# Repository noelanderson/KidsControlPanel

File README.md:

# KidsControlPanel
Octonaut's inspired vehicle control panel with flight yoke and standard instruments

Javascript application runs instrument cluster on Raspberry Pi displaying on a (800x400) lcd panel

Custom RP2040 based hardware runs the remaining panel functions

RP2040 board appears as a HID joystick and uses a VL6180X ranging sensor to measure pitch, and an AS5600 magnetic Rotation Sensor to measure roll.

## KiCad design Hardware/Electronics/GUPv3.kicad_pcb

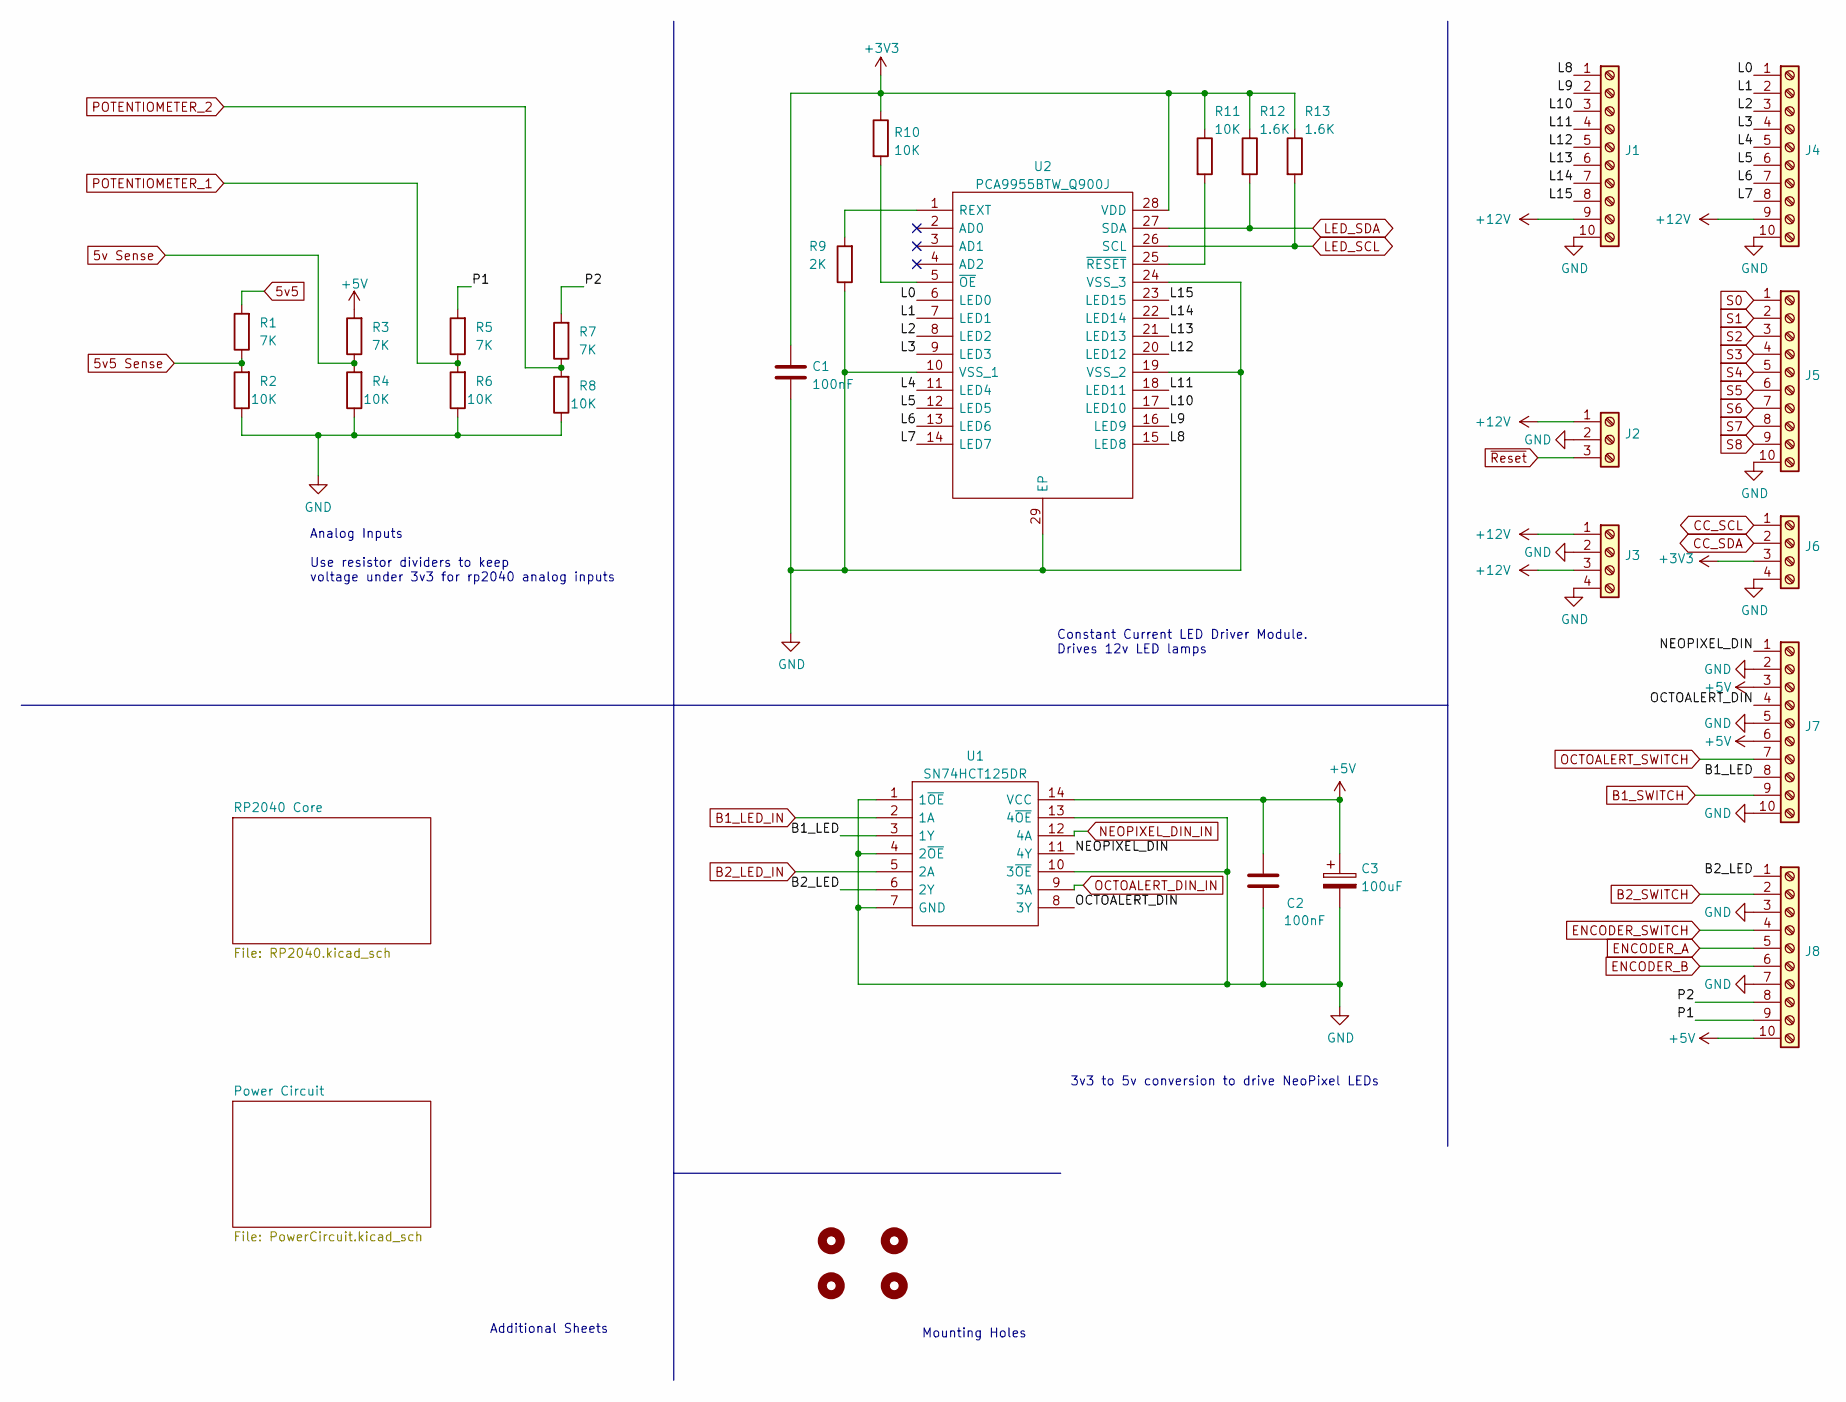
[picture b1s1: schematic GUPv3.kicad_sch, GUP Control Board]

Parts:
C1, C2: 100nF; C_1206_3216Metric_Pad1.33x1.80mm_HandSolder
C3: 100uF; C_1206_3216Metric_Pad1.33x1.80mm_HandSolder
H1, H2, H3, H4: M2.5; MountingHole_2.7mm_M2.5_DIN965_Pad
J1, J4, J5, J7, J8: Screw_Terminal_01x10; CUI_TB002-500-10BE
J2: Screw_Terminal_01x03; CUI_TB002-500-03BE
J3, J6: Screw_Terminal_01x04; CUI_TB002-500-04BE
R1, R3, R5, R7: 7K; R_1206_3216Metric_Pad1.30x1.75mm_HandSolder
R2, R4, R6, R8, R10, R11: 10K; R_1206_3216Metric_Pad1.30x1.75mm_HandSolder
R9: 2K; R_1206_3216Metric_Pad1.30x1.75mm_HandSolder
R12, R13: 1.6K; R_1206_3216Metric_Pad1.30x1.75mm_HandSolder
U1: SN74HCT125DR; SOIC127P600X175-14N; Mouser Part Number 595-SN74HCT125DR
U2: PCA9955BTW_Q900J; SOP65P640X110-29N_thermal_vias; Mouser Part Number 771-PCA9955BTW/Q900J

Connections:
5v5: R1.2; also elsewhere on the board
5v5 Sense: R1.1, R2.2; also elsewhere on the board
5v Sense: R3.1, R4.2; also elsewhere on the board
+3V3: C1.1, J6.3, R10.1, R11.1, R12.1, R13.1, U2.28 (VDD); also elsewhere on the board
+5V: C2.1, C3.1, J7.3, J7.6, J8.10, R3.2, U1.14 (VCC); also elsewhere on the board
+12V: J1.9, J2.1, J3.1, J3.3, J4.9; also elsewhere on the board
/B1_LED: J7.8, U1.3 (1Y)
/B2_LED: J8.1, U1.6 (2Y)
/L0: J4.1, U2.6 (LED0)
/L1: J4.2, U2.7 (LED1)
/L2: J4.3, U2.8 (LED2)
/L3: J4.4, U2.9 (LED3)
/L4: J4.5, U2.11 (LED4)
/L5: J4.6, U2.12 (LED5)
/L6: J4.7, U2.13 (LED6)
/L7: J4.8, U2.14 (LED7)
/L8: J1.1, U2.15 (LED8)
/L9: J1.2, U2.16 (LED9)
/L10: J1.3, U2.17 (LED10)
/L11: J1.4, U2.18 (LED11)
/L12: J1.5, U2.20 (LED12)
/L13: J1.6, U2.21 (LED13)
/L14: J1.7, U2.22 (LED14)
/L15: J1.8, U2.23 (LED15)
/NEOPIXEL_DIN: J7.1, U1.11 (4Y)
/OCTOALERT_DIN: J7.4, U1.8 (3Y)
/P1: J8.9, R5.2
/P2: J8.8, R7.2
B1_LED_IN: U1.2 (1A); also elsewhere on the board
B1_SWITCH: J7.9; also elsewhere on the board
B2_LED_IN: U1.5 (2A); also elsewhere on the board
B2_SWITCH: J8.2; also elsewhere on the board
CC_SCL: J6.1; also elsewhere on the board
CC_SDA: J6.2; also elsewhere on the board
ENCODER_A: J8.5; also elsewhere on the board
ENCODER_B: J8.6; also elsewhere on the board
ENCODER_SWITCH: J8.4; also elsewhere on the board
GND: C1.2, C2.2, C3.2, J1.10, J2.2, J3.2, J3.4, J4.10, J5.10, J6.4, J7.2, J7.5, J7.10, J8.3, J8.7, R2.1, R4.1, R6.1, R8.1, R9.1, U1.1 (1~OE), U1.4 (2~OE), U1.7 (GND), U1.10 (3~OE), U1.13 (4~OE), U2.10 (VSS_1), U2.19 (VSS_2), U2.24 (VSS_3), U2.29 (EP); also elsewhere on the board
LED_SCL: R13.2, U2.26 (SCL); also elsewhere on the board
LED_SDA: R12.2, U2.27 (SDA); also elsewhere on the board
NEOPIXEL_DIN_IN: U1.12 (4A); also elsewhere on the board
unnamed: R9.2, U2.1 (REXT)
unnamed: R10.2, U2.5 (~OE)
unnamed: R11.2, U2.25 (~RESET)
OCTOALERT_DIN_IN: U1.9 (3A); also elsewhere on the board
OCTOALERT_SWITCH: J7.7; also elsewhere on the board
POTENTIOMETER_1: R5.1, R6.2; also elsewhere on the board
POTENTIOMETER_2: R7.1, R8.2; also elsewhere on the board
S0: J5.1; also elsewhere on the board
S1: J5.2; also elsewhere on the board
S2: J5.3; also elsewhere on the board
S3: J5.4; also elsewhere on the board
S4: J5.5; also elsewhere on the board
S5: J5.6; also elsewhere on the board
S6: J5.7; also elsewhere on the board
S7: J5.8; also elsewhere on the board
S8: J5.9; also elsewhere on the board
~Reset: J2.3; also elsewhere on the board

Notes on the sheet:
3v3 to 5v conversion to drive NeoPixel LEDs
Analog Inputs Use resistor dividers to keep voltage under 3v3 for rp2040 analog inputs
Constant Current LED Driver Module. Drives 12v LED lamps
Additional Sheets
Mounting Holes

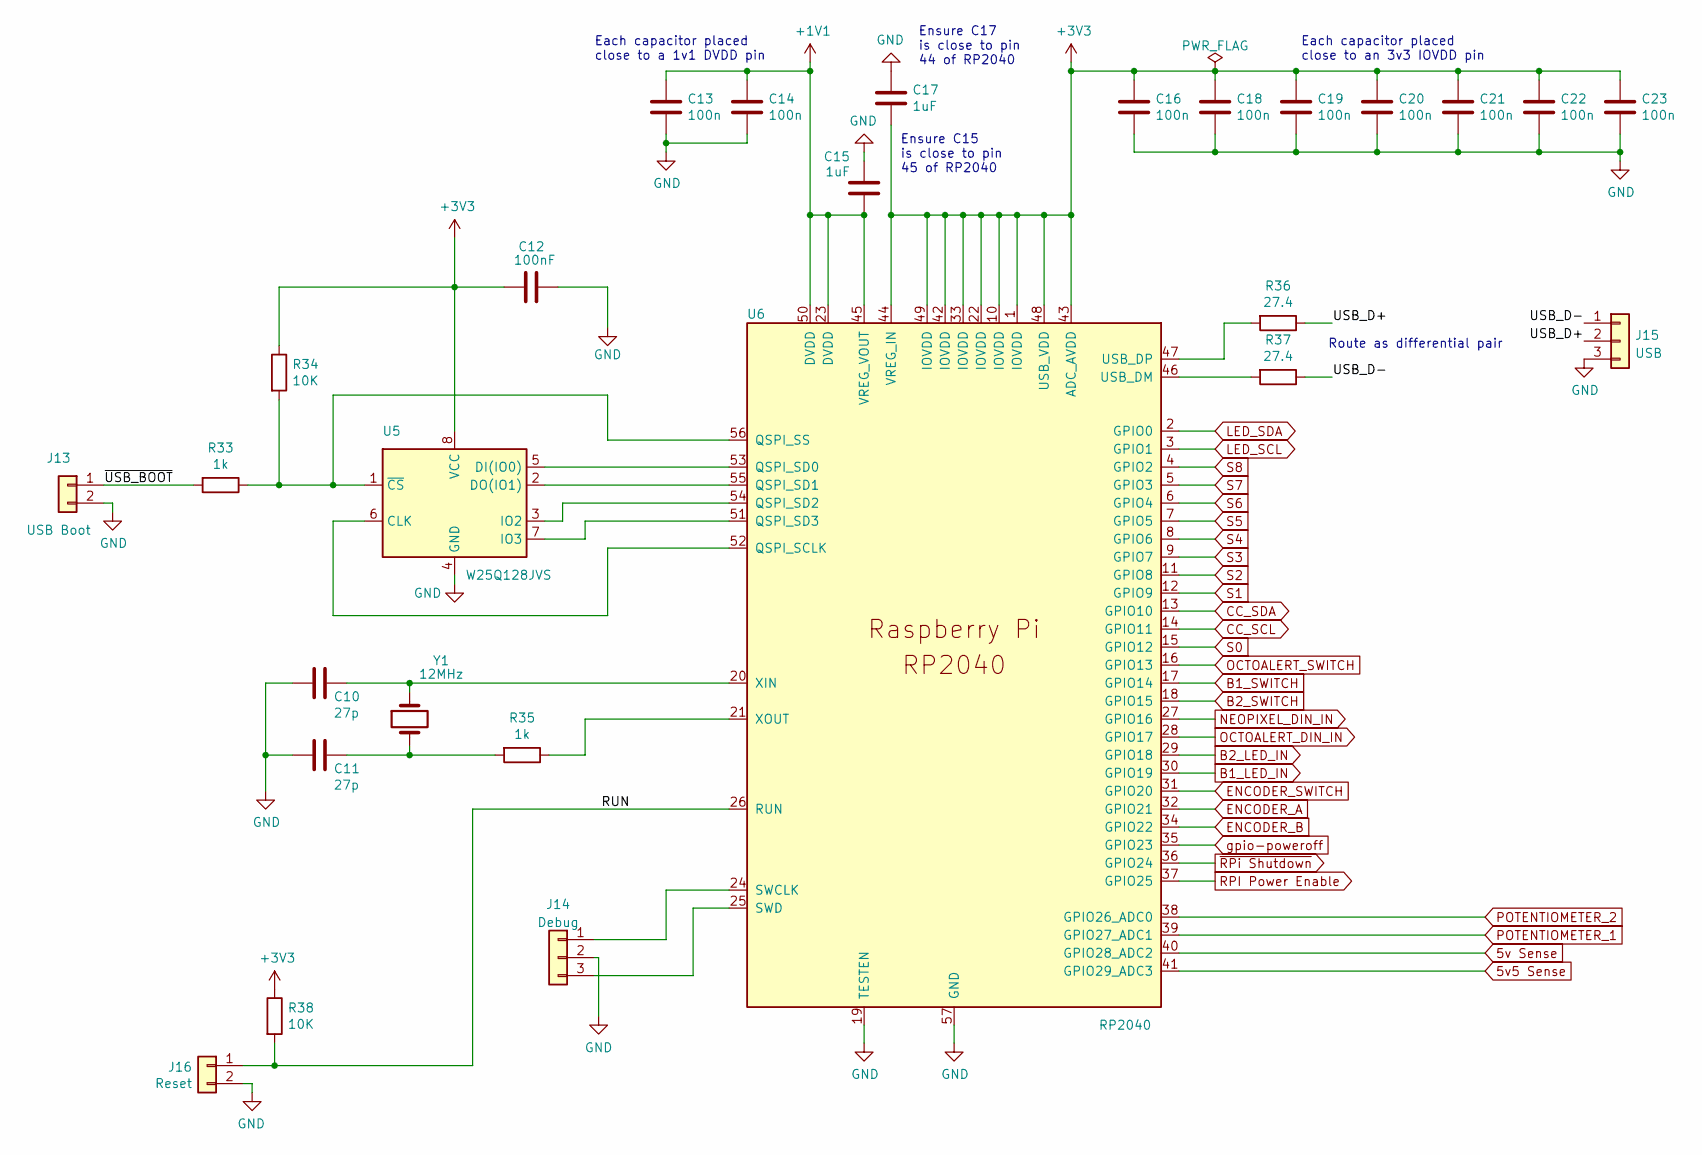
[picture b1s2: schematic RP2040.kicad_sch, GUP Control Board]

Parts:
C10, C11: 27p; C_1206_3216Metric_Pad1.33x1.80mm_HandSolder
C12: 100nF; C_1206_3216Metric_Pad1.33x1.80mm_HandSolder
C13, C14, C16, C18, C19, C20, C21, C22, C23: 100n; C_0603_1608Metric_Pad1.08x0.95mm_HandSolder
C15, C17: 1uF; C_0603_1608Metric_Pad1.08x0.95mm_HandSolder
J13: USB Boot; PinHeader_1x02_P2.54mm_Vertical
J14: Debug; PinHeader_1x03_P2.54mm_Vertical
J15: USB; PinHeader_1x03_P2.54mm_Vertical
J16: Reset; PinHeader_1x02_P2.54mm_Vertical
R33: 1k; R_1206_3216Metric_Pad1.30x1.75mm_HandSolder
R34: 10K; R_1206_3216Metric_Pad1.30x1.75mm_HandSolder
R35: 1k; R_0603_1608Metric_Pad0.98x0.95mm_HandSolder
R36, R37: 27.4; R_0603_1608Metric_Pad0.98x0.95mm_HandSolder
R38: 10K; R_0603_1608Metric_Pad0.98x0.95mm_HandSolder
U5: W25Q128JVS; SOIC127P790X216-8N
U6: RP2040; RP2040-QFN-56
Y1: 12MHz; ABLS7M216000MHZD2YT; Digi-Key_PN 535-13415-1-ND

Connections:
5v5 Sense: U6.41 (GPIO29_ADC3); also elsewhere on the board
5v Sense: U6.40 (GPIO28_ADC2); also elsewhere on the board
+1V1: C13.1, C14.1, C15.1, U6.23 (DVDD), U6.45 (VREG_VOUT), U6.50 (DVDD)
+3V3: C12.2, C16.1, C17.2, C18.1, C19.1, C20.1, C21.1, C22.1, C23.1, R34.1, R38.1, U5.8 (VCC), U6.1 (IOVDD), U6.10 (IOVDD), U6.22 (IOVDD), U6.33 (IOVDD), U6.42 (IOVDD), U6.43 (ADC_AVDD), U6.44 (VREG_IN), U6.48 (USB_VDD), U6.49 (IOVDD); also elsewhere on the board
/RP2040 Core/RUN: J16.1, R38.2, U6.26 (RUN)
/RP2040 Core/USB_D+: J15.2, R36.1
/RP2040 Core/USB_D-: J15.1, R37.1
/RP2040 Core/~USB_BOOT: J13.1, R33.2
B1_LED_IN: U6.30 (GPIO19); also elsewhere on the board
B1_SWITCH: U6.17 (GPIO14); also elsewhere on the board
B2_LED_IN: U6.29 (GPIO18); also elsewhere on the board
B2_SWITCH: U6.18 (GPIO15); also elsewhere on the board
CC_SCL: U6.14 (GPIO11); also elsewhere on the board
CC_SDA: U6.13 (GPIO10); also elsewhere on the board
ENCODER_A: U6.32 (GPIO21); also elsewhere on the board
ENCODER_B: U6.34 (GPIO22); also elsewhere on the board
ENCODER_SWITCH: U6.31 (GPIO20); also elsewhere on the board
GND: C10.2, C11.2, C12.1, C13.2, C14.2, C15.2, C16.2, C17.1, C18.2, C19.2, C20.2, C21.2, C22.2, C23.2, J13.2, J14.2, J15.3, J16.2, U5.4 (GND), U6.19 (TESTEN), U6.57 (GND); also elsewhere on the board
LED_SCL: U6.3 (GPIO1); also elsewhere on the board
LED_SDA: U6.2 (GPIO0); also elsewhere on the board
NEOPIXEL_DIN_IN: U6.27 (GPIO16); also elsewhere on the board
unnamed: C10.1, U6.20 (XIN), Y1.1
unnamed: C11.1, R35.2, Y1.2
unnamed: J14.1, U6.24 (SWCLK)
unnamed: J14.3, U6.25 (SWD)
unnamed: R33.1, R34.2, U5.1 (~CS), U6.56 (QSPI_SS)
unnamed: R35.1, U6.21 (XOUT)
unnamed: R36.2, U6.47 (USB_DP)
unnamed: R37.2, U6.46 (USB_DM)
unnamed: U5.2 (DO(IO1)), U6.55 (QSPI_SD1)
unnamed: U5.3 (IO2), U6.54 (QSPI_SD2)
unnamed: U5.5 (DI(IO0)), U6.53 (QSPI_SD0)
unnamed: U5.6 (CLK), U6.52 (QSPI_SCLK)
unnamed: U5.7 (IO3), U6.51 (QSPI_SD3)
OCTOALERT_DIN_IN: U6.28 (GPIO17); also elsewhere on the board
OCTOALERT_SWITCH: U6.16 (GPIO13); also elsewhere on the board
POTENTIOMETER_1: U6.39 (GPIO27_ADC1); also elsewhere on the board
POTENTIOMETER_2: U6.38 (GPIO26_ADC0); also elsewhere on the board
RPI Power Enable: U6.37 (GPIO25); also elsewhere on the board
S0: U6.15 (GPIO12); also elsewhere on the board
S1: U6.12 (GPIO9); also elsewhere on the board
S2: U6.11 (GPIO8); also elsewhere on the board
S3: U6.9 (GPIO7); also elsewhere on the board
S4: U6.8 (GPIO6); also elsewhere on the board
S5: U6.7 (GPIO5); also elsewhere on the board
S6: U6.6 (GPIO4); also elsewhere on the board
S7: U6.5 (GPIO3); also elsewhere on the board
S8: U6.4 (GPIO2); also elsewhere on the board
gpio-poweroff: U6.35 (GPIO23); also elsewhere on the board
~RPi Shutdown: U6.36 (GPIO24); also elsewhere on the board

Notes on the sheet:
Route as differential pair
Ensure C15 is close to pin 45 of RP2040
Each capacitor placed close to an 3v3 IOVDD pin
Ensure C17 is close to pin 44 of RP2040
Each capacitor placed close to a 1v1 DVDD pin

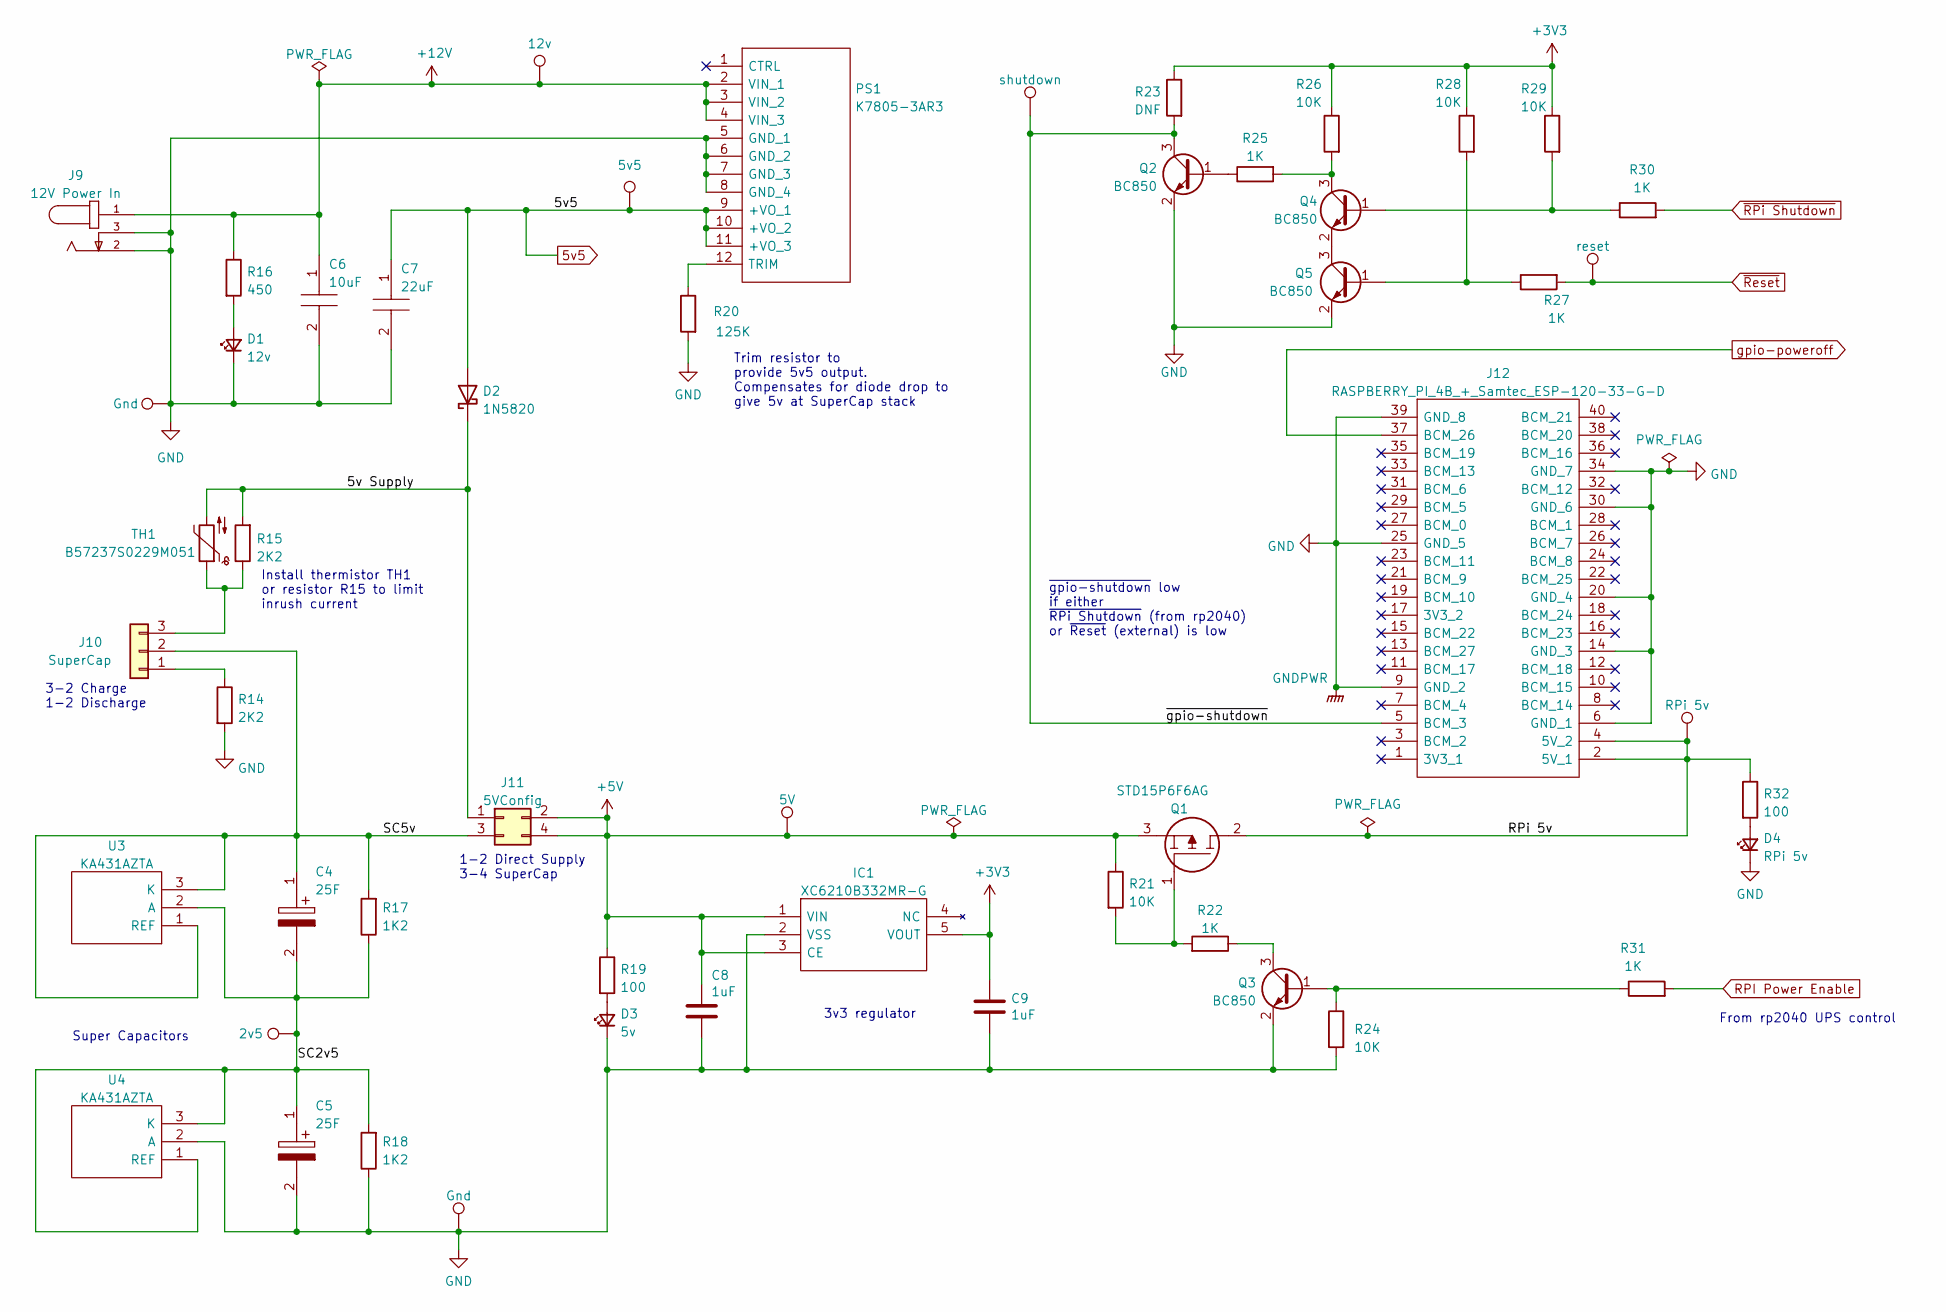
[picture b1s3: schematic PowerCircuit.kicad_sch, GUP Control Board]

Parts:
C4, C5: 25F; CAPPRD730W85D1650H2700; Mouser Part Number 581-SCCU25B256SRB
C6: 10uF; FG20; Mouser Part Number 810-FG20X7S1H106KRT6
C7: 22uF; FK20; Mouser Part Number N/A
C8, C9: 1uF; C_1206_3216Metric_Pad1.33x1.80mm_HandSolder
D1: 12v; LED_1210_3225Metric_Pad1.42x2.65mm_HandSolder
D2: 1N5820; D_DO-201AD_P15.24mm_Horizontal
D3: 5v; LED_1210_3225Metric_Pad1.42x2.65mm_HandSolder
D4: RPi 5v; LED_1210_3225Metric_Pad1.42x2.65mm_HandSolder
IC1: XC6210B332MR-G; SOT95P280X130-5N; Mouser Part Number 865-XC6210B332MR-G
J9: 12V Power In; PJ-102AH; PART_REV 1.02
J10: SuperCap; PinHeader_1x03_P2.54mm_Vertical
J11: 5VConfig; PinHeader_2x02_P2.54mm_Vertical
J12: RASPBERRY_PI_4B_+_Samtec_ESP-120-33-G-D; RASPBERRYPI4B4GB; Manufacturer_Part_Number RASPBERRY PI 4B + Samtec ESP-120-33-G-D
PS1: K7805-3AR3; K78053AR3; Manufacturer_Part_Number K7805-3AR3
Q1: STD15P6F6AG; STD36P4LLF6; Mouser Part Number 511-STD15P6F6AG
Q2, Q3, Q4, Q5: BC850; SOT-23
R14, R15: 2K2; R_Axial_DIN0516_L15.5mm_D5.0mm_P20.32mm_Horizontal
R16: 450; R_1206_3216Metric_Pad1.30x1.75mm_HandSolder
R17, R18: 1K2; R_Axial_DIN0207_L6.3mm_D2.5mm_P10.16mm_Horizontal
R19, R32: 100; R_1206_3216Metric_Pad1.30x1.75mm_HandSolder
R20: 125K; R_Axial_DIN0207_L6.3mm_D2.5mm_P10.16mm_Horizontal
R21, R24, R26, R28, R29: 10K; R_1206_3216Metric_Pad1.30x1.75mm_HandSolder
R22, R25, R27, R30, R31: 1K; R_1206_3216Metric_Pad1.30x1.75mm_HandSolder
R23: DNF; R_1206_3216Metric_Pad1.30x1.75mm_HandSolder
TH1: B57237S0229M051
TP1, TP4: Gnd; 4952
TP2: 2v5; 4952
TP3: 12v; 4952
TP5: 5v5; 4952
TP6: 5V; 4952
TP7: shutdown; 4952
TP8: reset; 4952
TP9: RPi 5v; 4952
U3, U4: KA431AZTA; Mouser Part Number 512-KA431AZTA

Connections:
5v5: C7.1, D2.2 (A), PS1.9 (+VO_1), PS1.10 (+VO_2), PS1.11 (+VO_3), TP5.1; also elsewhere on the board
+3V3: C9.1, IC1.5 (VOUT), R23.1, R26.1, R28.1, R29.1; also elsewhere on the board
+5V: C8.1, IC1.1 (VIN), IC1.3 (CE), J11.2, J11.4, Q1.3, R19.1, R21.1, TP6.1; also elsewhere on the board
+12V: C6.1, J9.1, PS1.2 (VIN_1), PS1.3 (VIN_2), PS1.4 (VIN_3), R16.1, TP3.1; also elsewhere on the board
/Power Circuit/5v Supply: D2.1 (K), J11.1, R15.2, TH1.2
/Power Circuit/RPi 5v: J12.2 (5V_1), J12.4 (5V_2), Q1.2, R32.1, TP9.1
/Power Circuit/SC2v5: C4.2, C5.1, R17.1, R18.2, TP2.1, U3.2 (A), U4.1 (REF), U4.3 (K)
/Power Circuit/SC5v: C4.1, J10.2, J11.3, R17.2, U3.1 (REF), U3.3 (K)
/Power Circuit/~gpio-shutdown: J12.5 (BCM_3), Q2.3 (C), R23.2, TP7.1
GND: C5.2, C6.2, C7.2, C8.2, C9.2, D1.1 (K), D3.1 (K), D4.1 (K), IC1.2 (VSS), J9.2, J9.3, J12.6 (GND_1), J12.9 (GND_2), J12.14 (GND_3), J12.20 (GND_4), J12.25 (GND_5), J12.30 (GND_6), J12.34 (GND_7), J12.39 (GND_8), PS1.5 (GND_1), PS1.6 (GND_2), PS1.7 (GND_3), PS1.8 (GND_4), Q2.2 (E), Q3.2 (E), Q5.2 (E), R14.2, R18.1, R20.2, R24.2, TP1.1, TP4.1, U4.2 (A); also elsewhere on the board
unnamed: D1.2 (A), R16.2
unnamed: D3.2 (A), R19.2
unnamed: D4.2 (A), R32.2
unnamed: J10.1, R14.1
unnamed: J10.3, R15.1, TH1.1
unnamed: PS1.12 (TRIM), R20.1
unnamed: Q1.1, R21.2, R22.2
unnamed: Q2.1 (B), R25.1
unnamed: Q3.1 (B), R24.1, R31.1
unnamed: Q3.3 (C), R22.1
unnamed: Q4.1 (B), R29.2, R30.1
unnamed: Q4.2 (E), Q5.3 (C)
unnamed: Q4.3 (C), R25.2, R26.2
unnamed: Q5.1 (B), R27.1, R28.2
RPI Power Enable: R31.2; also elsewhere on the board
gpio-poweroff: J12.37 (BCM_26); also elsewhere on the board
~RPi Shutdown: R30.2; also elsewhere on the board
~Reset: R27.2, TP8.1; also elsewhere on the board

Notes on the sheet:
1-2 Direct Supply 3-4 SuperCap
Trim resistor to provide 5v5 output. Compensates for diode drop to give 5v at SuperCap stack
~{gpio-shutdown} low if either ~{RPi Shutdown} (from rp2040) or ~{Reset} (external) is low
From rp2040 UPS control
Install thermistor TH1 or resistor R15 to limit inrush current
3v3 regulator
Super Capacitors
3-2 Charge 1-2 Discharge

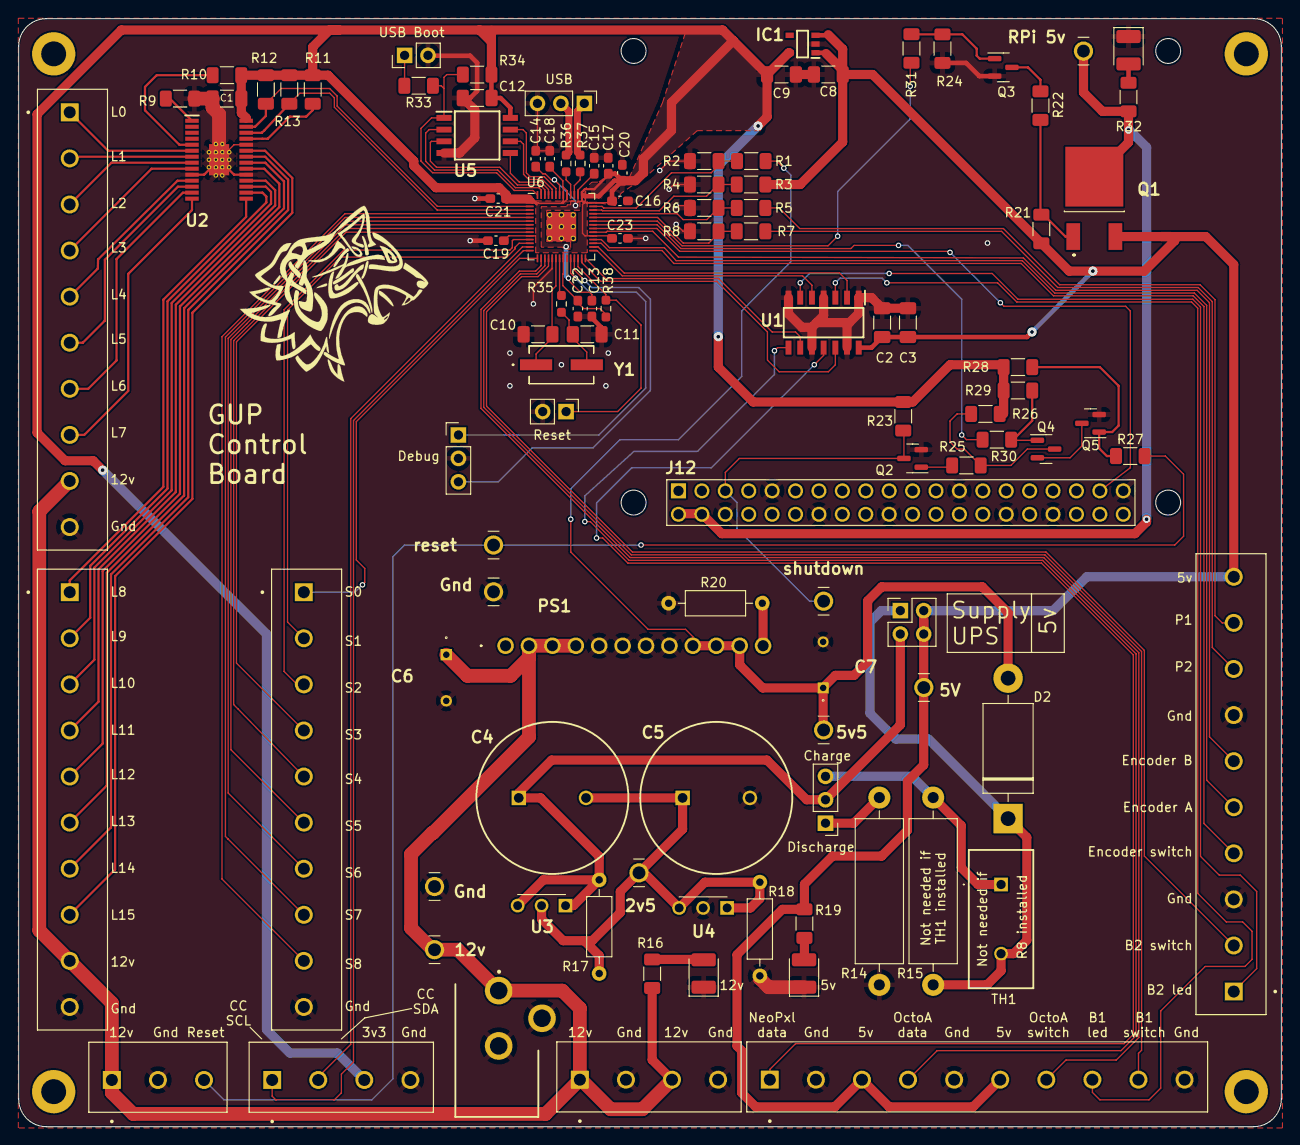
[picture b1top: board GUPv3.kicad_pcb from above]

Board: 2 copper layers, 137.0 x 120.2 mm, 109 parts (0 on the bottom side), 98 nets.

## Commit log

2022-08-09 dadd dashboard image
2022-09-04 Driver for PCA9955
2022-11-20 Flight Instrument updates
2022-11-20 Comment refesh
